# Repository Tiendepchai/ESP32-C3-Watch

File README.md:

# ESP32-C3 ANCS Watch

**ESP32-C3 ANCS Watch** is an ESP-IDF firmware project for a compact BLE watch-style accessory.  
It pairs with an iPhone, subscribes to Apple Notification Center Service (ANCS), fetches notification attributes, synchronizes time, and renders notifications on a 128 × 64 SH1106 OLED display.

> **Project status:** Active firmware prototype. The core BLE/ANCS/display flow is implemented; power monitoring and iOS companion features are optional or under development.

---

## Table of Contents

- [Overview](#overview)
- [Key Features](#key-features)
- [System Architecture](#system-architecture)
- [Hardware](#hardware)
- [Firmware Layout](#firmware-layout)
- [Notification Ordering](#notification-ordering)
- [Getting Started](#getting-started)
- [Build and Flash](#build-and-flash)
- [Usage](#usage)
- [Testing Checklist](#testing-checklist)
- [Troubleshooting](#troubleshooting)
- [Roadmap](#roadmap)
- [License](#license)

---

## Overview

The firmware implements the standard ANCS accessory flow:

1. The ESP32-C3 advertises as a BLE peripheral.
2. The iPhone connects and creates a secure BLE bond.
3. After encryption is enabled, the ESP32-C3 switches role logically to a GATT client and discovers ANCS on the iPhone.
4. The ESP32-C3 subscribes to the ANCS Notification Source and Data Source characteristics.
5. For each notification UID, the firmware requests:
   - `AppIdentifier`
   - `Title`
   - `Message`
   - `Date`
6. Notifications are stored locally and sorted with the newest notification first.
7. The display manager renders connection status, watchface, notification detail, and navigation views.

---

## Key Features

- BLE pairing and bonding powered by NimBLE.
- Bonded reconnect flow using directed advertising first, then general advertising fallback.
- ANCS discovery, CCCD subscription, notification event handling, and attribute parsing.
- Date-based notification ordering using ANCS `Date` when available.
- Temporary local receive timestamp while waiting for notification attributes.
- iOS Current Time Service client for watchface time synchronization.
- SH1106 128 × 64 OLED rendering for:
  - connection status
  - watchface
  - notification list/detail
  - navigation state
- In-memory notification store with configurable filtering.
- NVS-backed settings and bond state persistence.
- Two-button physical control for:
  - notification navigation
  - clearing notifications
  - changing filters
  - resetting bond state
- Optional SwiftUI companion scaffold for future configuration and navigation handoff.

---

## System Architecture

```text
┌────────────────────┐
│      iPhone        │
│  ANCS + CTS Server │
└─────────┬──────────┘
          │ BLE encrypted link
          ▼
┌──────────────────────────────────────┐
│              ESP32-C3                │
│                                      │
│  ┌───────────────┐   ┌────────────┐  │
│  │ BLE Manager   │──▶│ ANCS Client│  │
│  └───────┬───────┘   └─────┬──────┘  │
│          │                 │         │
│          ▼                 ▼         │
│  ┌───────────────┐   ┌─────────────┐ │
│  │ CTS Client    │   │ Notification│ │
│  │ Time Sync     │   │ Store       │ │
│  └───────┬───────┘   └─────┬───────┘ │
│          │                 │         │
│          ▼                 ▼         │
│  ┌────────────────────────────────┐  │
│  │        Display Manager         │  │
│  │      SH1106 OLED Rendering     │  │
│  └────────────────────────────────┘  │
│                                      │
│  ┌────────────────────────────────┐  │
│  │        Storage Manager         │  │
│  │        NVS Settings/Bonds      │  │
│  └────────────────────────────────┘  │
└──────────────────────────────────────┘
```

---

## Hardware

| Component | Specification |
| --- | --- |
| MCU | ESP32-C3 |
| Display | SH1106 128 × 64 OLED |
| Display bus | I2C |
| Button A | GPIO3, active low |
| Button B | GPIO4, active low |

### Default Wiring

| Function | ESP32-C3 Pin |
| --- | --- |
| OLED VCC | 3V3 |
| OLED GND | GND |
| OLED SDA | GPIO6 |
| OLED SCL | GPIO7 |
| Button A | GPIO3 to GND |
| Button B | GPIO4 to GND |

Board-level constants are defined in:

```text
components/board_config/include/board_config.h
```

---

## Firmware Layout

| Path | Purpose |
| --- | --- |
| `main/` | Application state machine, UI flow, and event orchestration |
| `components/ble_manager/` | NimBLE initialization, advertising, bonding, reconnect, and config GATT service |
| `components/ancs_client/` | ANCS discovery, notification subscription, attribute request, and response parser |
| `components/cts_client/` | iOS Current Time Service client |
| `components/display_manager/` | SH1106 driver, framebuffer, watchface rendering, and notification rendering |
| `components/notification_store/` | In-memory notification storage, filtering, and sorting |
| `components/storage_manager/` | NVS-backed settings and persistent state |
| `components/power_manager/` | Optional battery and power monitoring |
| `ios/ANCSWatchConfig/` | Optional SwiftUI companion app scaffold |

---

## Notification Ordering

The notification ordering pipeline is designed to avoid relying only on local receive time.

```text
ANCS Notification Source event
        │
        ▼
Extract NotificationUID
        │
        ▼
Request attributes:
AppIdentifier, Title, Message, Date
        │
        ▼
Parse ANCS Data Source response
        │
        ▼
Use ANCS Date if available
        │
        ▼
Update notification record
        │
        ▼
Sort newest first
```

When a notification event first arrives, the firmware stores it with the local receive timestamp as a temporary value.  
After the ANCS `Date` attribute is fetched, the stored record is updated and the notification list is re-sorted by timestamp in descending order.

This allows notifications such as:

```text
Messenger  - 1 second ago
MoMo       - 2 minutes ago
```

to appear in the expected order, with the newest notification at the top.

---

## Getting Started

### Prerequisites

Install and configure:

- ESP-IDF v6.0 or newer
- Python environment required by ESP-IDF
- USB serial driver for your ESP32-C3 board
- An iPhone with Bluetooth enabled
- Optional: nRF Connect for BLE debugging

### Clone the Repository

```bash
git clone <your-repository-url>
cd esp32-c3-ancs-watch
```

### Set the ESP-IDF Target

```bash
idf.py set-target esp32c3
```

---

## Build and Flash

### Activate ESP-IDF

Use the activation script generated by your ESP-IDF installation.

Example:

```bash
source "$HOME/.espressif/tools/activate_idf_v6.0.sh"
```

Alternatively, if ESP-IDF is installed globally:

```bash
. "$IDF_PATH/export.sh"
```

### Build

```bash
idf.py build
```

### Flash

Replace the port with the serial device used by your board.

```bash
idf.py -p /dev/cu.usbmodemXXXX flash
```

### Monitor Logs

```bash
idf.py -p /dev/cu.usbmodemXXXX monitor
```

### Flash and Monitor in One Command

```bash
idf.py -p /dev/cu.usbmodemXXXX flash monitor
```

---

## Usage

### First Pairing

1. Flash the firmware to the ESP32-C3.
2. Open the Bluetooth settings on iOS.
3. Select the ESP32-C3 accessory.
4. Accept the pairing request.
5. Wait until the BLE link is encrypted and ANCS discovery completes.
6. Send a test notification to the iPhone.
7. Verify that the OLED displays the notification.

### Reconnect Flow

After a successful bond, the firmware tries:

1. Directed advertising to the bonded iPhone.
2. General advertising fallback if directed reconnect fails.
3. ANCS rediscovery after the encrypted link is restored.

### Button Controls

| Action | Expected Behavior |
| --- | --- |
| Button A | Navigate through notifications or UI views |
| Button B | Change filter, clear notification, or trigger secondary action |
| Long press / configured combo | Reset bond state or enter maintenance flow |

> Exact button behavior depends on the current firmware state machine and board configuration.

---

## Testing Checklist

Before testing a first-pair flow:

- Clear the iOS Bluetooth bond for the ESP32-C3.
- Clear stored bonds on the ESP32-C3.
- Reboot both devices if bonding behavior is inconsistent.

Recommended validation sequence:

- Pair from iOS or nRF Connect.
- Confirm the first bond is retained locally.
- Check logs for:

```text
bond store peers after secure=1
```

- Wait for:

```text
ANCS ready, attrs=enabled
```

- Send several notifications from different apps.
- Verify that notification details are fetched correctly.
- Verify that notifications are sorted by ANCS `Date`.
- Walk out of range to force a disconnect.
- Return to range and confirm bonded reconnect works.
- Confirm pre-existing or pending notifications can wake the display and render correctly.
- Test button navigation, filter changes, clear action, and bond reset.

---

## Troubleshooting

### ANCS does not become ready

Check that:

- The iPhone accepted the BLE pairing request.
- The connection is encrypted.
- The ESP32-C3 bond was not erased after pairing.
- ANCS discovery runs only after encryption.
- Notification permissions are enabled on iOS.

Useful log marker:

```text
ANCS ready, attrs=enabled
```

### Notifications appear but details are missing

Check that:

- Data Source subscription succeeded.
- Control Point writes are accepted.
- `GetNotificationAttributes` is sent with the correct `NotificationUID`.
- The parser handles fragmented Data Source responses.

### Notification order is incorrect

Check that:

- `Date` is included in the requested ANCS attributes.
- The firmware updates the temporary receive timestamp after `Date` arrives.
- The notification store re-sorts the list after attribute parsing.

### Reconnect does not work

Check that:

- Bond data is stored in NVS.
- Directed advertising uses the bonded peer address.
- General advertising fallback starts after directed advertising fails.
- iOS still has the accessory saved in Bluetooth settings.

### macOS ESP-IDF `platform.mac_ver()` issue

If the local Python environment fails because of a macOS version parsing issue, use a clean ESP-IDF Python environment first.  
If the issue persists, the following development workaround can be used:

```bash
IDF_COMPONENT_MANAGER=0 python -c 'import os, platform, runpy, sys; tools=os.path.join(os.environ["IDF_PATH"],"tools"); sys.path.insert(0,tools); platform.mac_ver=lambda release="", versioninfo=("", "", ""), machine="": ("26.1", ("", "", ""), os.uname().machine); sys.argv=[os.path.join(tools,"idf.py")]+sys.argv[1:]; runpy.run_path(sys.argv[0], run_name="__main__")' build
```

---

## Roadmap

- [ ] Add battery percentage monitoring.
- [ ] Add charging status display.
- [ ] Improve notification grouping by app.
- [ ] Add persistent notification history if required.
- [ ] Finalize iOS SwiftUI companion app.
- [ ] Add configurable button actions.
- [ ] Add screenshots or hardware photos.
- [ ] Add CI build workflow for ESP-IDF.
- [ ] Add release binaries and flashing instructions.

---

## License

This project is licensed under the MIT License. See [LICENSE](LICENSE) for details.

---

## Vietnamese Summary

**ESP32-C3 ANCS Watch** là firmware ESP-IDF cho thiết bị đeo nhỏ dùng BLE. Thiết bị ghép đôi với iPhone, subscribe Apple Notification Center Service, lấy thông tin `AppIdentifier`, `Title`, `Message`, `Date`, sau đó hiển thị thông báo lên OLED SH1106 128 × 64.

Điểm chính:

- Pairing/bonding BLE bằng NimBLE.
- Tự reconnect với iPhone đã bond.
- Fetch chi tiết thông báo qua ANCS.
- Sort thông báo theo `Date` để thông báo mới nhất hiện trên đầu.
- Đồng bộ giờ qua iOS Current Time Service.
- Hiển thị watchface và notification bằng SH1106 OLED.
- Lưu cấu hình bằng NVS.
- Điều khiển bằng hai nút vật lý.

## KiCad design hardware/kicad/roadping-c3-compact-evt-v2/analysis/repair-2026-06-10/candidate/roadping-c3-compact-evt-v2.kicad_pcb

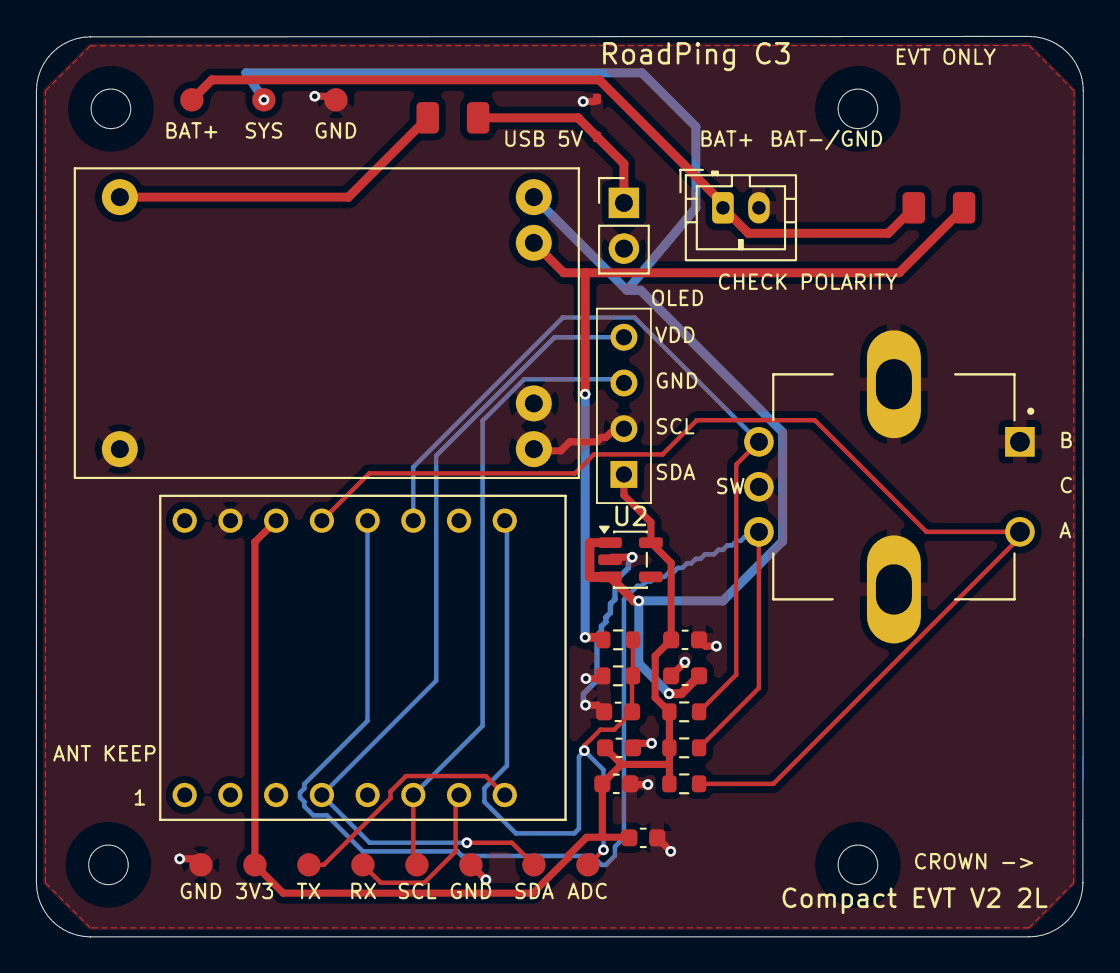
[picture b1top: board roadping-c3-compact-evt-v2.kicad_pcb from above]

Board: 2 copper layers, 58.2 x 50.0 mm, 31 parts (0 on the bottom side), 15 nets.

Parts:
C1, C2: 1uF; C_0603_1608Metric
C3: 10uF; C_0603_1608Metric
C4, C5, C9: 100nF; C_0603_1608Metric
D1: USB_5V_TVS; D_SOD-323
DS1: SH1106_I2C_OLED; OLED_4PIN_VDD_GND_SCK_SDA_2.54MM
F1: PTC_USB_5V_1A; Fuse_1206_3216Metric
F2: PTC_BAT_1A; Fuse_1206_3216Metric
J1: USB_5V_INPUT; PinHeader_1x02_P2.54mm_Vertical
J2: JST_PH_2PIN_LIPO; JST_PH_B2B-PH-K_1x02_P2.00mm_Vertical
J3: UART_DEBUG_PROGRAM; TESTPADS_1X06_2.54MM_EVT
MH1, MH2, MH3, MH4: M2_NPTH; MountingHole_M2_NPTH_5mmKeepout
R3, R4, R5: 10k; R_0603_1608Metric
R6: 220k; R_0603_1608Metric
R7: 100k; R_0603_1608Metric
SW1: PEC11R-4215F-S0024; XDCR_PEC11R-4215F-S0024
TP2: BAT_CONN+; TP_Round_1.0mm
TP3: SYS_RAW; TP_Round_1.0mm
TP5: GND; TP_Round_1.0mm
TP8: I2C_SDA; TP_Round_1.0mm
TP13: BAT_ADC; TP_Round_1.0mm
U1: TP4056-Module
U2: AP2112K-3.3; SOT-23-5
U3: ESP32-C3_SUPERMINI_TH; MODULE_ESP32-C3_SUPERMINI_TH

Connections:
/3V3: C2.1, C3.1, C4.1, C5.1, DS1.1 (VDD), J3.2, R3.1, R4.1, R5.1, U2.5 (VOUT), U3.3.3 (3V3)
/BAT_ADC: C9.1, R6.2, R7.1, TP13.1 (1_1), U3.0 (GPIO0)
/BAT_CONN+: F2.1, J2.1 (BAT+), TP2.1 (1_1)
/ENC_A: R3.2, SW1.A, U3.2 (GPIO2)
/ENC_B: R4.2, SW1.B, U3.3 (GPIO3)
/ENC_SW: R5.2, SW1.2 (SW2), U3.4 (GPIO4)
/GND: C1.2, C2.2, C3.2, C4.2, C5.2, C9.2, D1.1, DS1.2 (GND), J1.2, J2.2 (BAT-), J3.1, J3.6, R7.2, SW1.1 (SW1), SW1.C, SW1.S1 (SHIELD1), SW1.S2 (SHIELD2), TP5.1 (1_1), U1.2 (IN-), U1.4 (OUT-), U1.6 (B-), U2.2 (GND), U3.G (GND)
/I2C_SCL: DS1.3 (SCK), J3.5, U3.10 (GPIO10)
/I2C_SDA: DS1.4 (SDA), TP8.1 (1_1), U3.8 (GPIO8)
/SYS_RAW: C1.1, TP3.1 (1_1), U1.3 (OUT+), U2.1 (VIN), U2.3 (EN)
/UART_RX: J3.4, U3.20 (GPIO20)
/UART_TX: J3.3, U3.21 (GPIO21)
/USB_5V: F1.2, U1.1 (IN+)
/USB_5V_IN: D1.2, F1.1, J1.1
/VBAT: F2.2, R6.1, U1.5 (B+)

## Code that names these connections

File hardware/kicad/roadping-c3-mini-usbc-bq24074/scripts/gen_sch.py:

#!/usr/bin/env python3
"""RoadPing C3 Mini KiCad 10 schematic generator — CLEAN"""
import os, uuid as _u, subprocess, json
from datetime import date

PROJ = os.path.dirname(os.path.dirname(os.path.abspath(__file__)))
SCH = os.path.join(PROJ, "roadping-c3-mini-usbc-bq24074.kicad_sch")
U = lambda: str(_u.uuid4())
G = 2.54; grd = lambda v: round(v/G)*G
_ = lambda x: f'\t\t{x}'  # indent level

def gl(name,x,y,o=0): return f'\t(global_label "{name}" (shape input) (at {grd(x)} {grd(y)} {o}) (effects (font (size 1.27 1.27))) (uuid "{U()}"))'
def w(x1,y1,x2,y2): return f'\t(wire (pts (xy {grd(x1)} {grd(y1)}) (xy {grd(x2)} {grd(y2)})) (stroke (width 0) (type default)) (uuid "{U()}"))'
def ll(name,x,y): return f'\t(label "{name}" (at {grd(x)} {grd(y)} 0) (effects (font (size 1.27 1.27))) (uuid "{U()}"))'

def SYM(lib_id, ref, val, x, y, fp="", ds=""):
    x,y = grd(x), grd(y); u = U()
    p = [f'(property "Reference" "{ref}" (at {x} {y-3.81} 0) (show_name no) (do_not_autoplace no) (effects (font (size 1.27 1.27))))',
         f'(property "Value" "{val}" (at {x} {y+3.81} 0) (show_name no) (do_not_autoplace no) (effects (font (size 1.27 1.27))))']
    if fp: p.append(f'(property "Footprint" "{fp}" (at {x} {y} 0) (hide yes) (show_name no) (do_not_autoplace no) (effects (font (size 1.27 1.27))))')
    if ds: p.append(f'(property "Datasheet" "{ds}" (at {x} {y} 0) (hide yes) (show_name no) (do_not_autoplace no) (effects (font (size 1.27 1.27))))')
    return f'\n\t(symbol (lib_id "{lib_id}") (at {x} {y} 0) (unit 1) (exclude_from_sim no) (in_bom yes) (on_board yes) (uuid "{u}")\n\t\t{chr(10).join(p)}\n\t)'

def GND(x,y):
    x,y = grd(x), grd(y); u = U()
    return f'\n\t(symbol (lib_id "roadping-c3:GND") (at {x} {y} 0) (unit 1) (in_bom no) (on_board no) (uuid "{u}") (property "Value" "GND" (at {x} {y+2.54} 0) (show_name no) (do_not_autoplace no) (effects (font (size 1.27 1.27)))))'

def PWR(x,y):
    x,y = grd(x), grd(y); u = U()
    return f'\n\t(symbol (lib_id "roadping-c3:PWR_FLAG") (at {x} {y} 0) (unit 1) (in_bom no) (on_board no) (uuid "{u}") (property "Value" "PWR_FLAG" (at {x} {y+2.54} 0) (show_name no) (do_not_autoplace no) (effects (font (size 1.27 1.27)))))'

# ── Build ─────────────────────────────────────────────────────
L = []
L.append(f'(kicad_sch\n\t(version 20260306)\n\t(generator "eeschema")\n\t(generator_version "10.0")\n\t(uuid "{U()}")\n\t(paper "A4")\n\t(title_block\n\t\t(title "RoadPing C3 Mini - USB-C + BQ24074")\n\t\t(date "{date.today().isoformat()}")\n\t\t(rev "schematic-draft")\n\t\t(company "RoadPing")\n\t)')

# Embed symbols from a file read
embed_file = os.path.join(PROJ, 'scripts', 'EMBED.txt')
if os.path.exists(embed_file):
    with open(embed_file) as f:
        embed = f.read()
else:
    embed = ''
    sys.stderr.write("WARNING: EMBED.txt not found, creating minimal schematic\n")

L.append(f'\t(lib_symbols\n{embed}\t)')

# 1. USB-C
L.append(SYM("Connector_USB:USB_C_Receptacle_USBIF","J1","TYPE-C-31-M-12",50.8,50.8,fp="Connector_USB:USB_C_Receptacle_HRO_TYPE-C-31-M-12"))
L.append(SYM("roadping-c3:Fuse","F1","PTC 1.1A",76.2,50.8))
L.append(SYM("roadping-c3:D_TVS","D1","PESD5V0S1BA",76.2,68.58))
L.append(SYM("roadping-c3:R","R1","5.1k",76.2,78.74))
L.append(SYM("roadping-c3:R","R2","5.1k",76.2,86.36))
L.append(SYM("Interface_Protection:USBLC6-2SC6","D2","USBLC6-2SC6",106.68,53.34))
L.append(w(60.96,50.8,76.2,50.8))
L.append(gl("VBUS",76.2,63.5)); L.append(w(76.2,58.42,76.2,68.58)); L.append(GND(76.2,71.12))
L.append(ll("CC1",66.04,78.74)); L.append(w(66.04,78.74,76.2,78.74)); L.append(GND(76.2,81.28))
L.append(ll("CC2",66.04,86.36)); L.append(w(66.04,86.36,76.2,86.36)); L.append(GND(76.2,88.9))
L.append(ll("USB_DP",66.04,43.18)); L.append(ll("USB_DN",66.04,38.1))
L.append(w(66.04,43.18,96.52,43.18)); L.append(w(66.04,38.1,96.52,38.1))
L.append(gl("USB_DP",115.06,43.18)); L.append(gl("USB_DN",115.06,38.1))

# 2. BQ24074
L.append(SYM("Battery_Management:BQ24074_RGT","U1","BQ24074RGTR",50.8,119.38,fp="Package_DFN_QFN:WQFN-20-1EP_3.5x3.5mm_P0.5mm_EP2.7x2.7mm",ds="https://www.ti.com/lit/ds/symlink/bq24074.pdf"))
L.append(gl("VBUS",40.64,119.38)); L.append(w(40.64,119.38,50.8,119.38))
L.append(SYM("roadping-c3:R","R3","1.1k",33.02,137.16))
L.append(SYM("roadping-c3:R","R4","2.0k",33.02,142.24))
L.append(GND(33.02,133.35)); L.append(GND(33.02,138.43))
L.append(SYM("roadping-c3:R","R5","10k",73.66,129.54))
L.append(SYM("roadping-c3:R","R6","10k",73.66,134.62))
L.append(GND(73.66,137.16))
L.append(SYM("roadping-c3:R","R_CE","10k",76.2,109.22))
L.append(SYM("roadping-c3:R","R_CHG","10k",76.2,104.14))
L.append(SYM("roadping-c3:R","R_FLT","10k",76.2,99.06))
L.append(gl("3V3",83.82,114.3)); L.append(gl("CE_CHG",83.82,109.22))
L.append(gl("CHG_STAT",83.82,104.14)); L.append(gl("FLT_STAT",83.82,99.06))
L.append(gl("SYS_RAW",76.2,119.38)); L.append(gl("VBAT",76.2,127.0))

# 3. AP2112K + LiPo
L.append(SYM("roadping-c3:AP2112K-3.3","U2","AP2112K-3.3",139.7,119.38))
L.append(SYM("roadping-c3:C","C1","1uF",129.54,129.54))
L.append(SYM("roadping-c3:C","C2","1uF",129.54,134.62))
L.append(SYM("roadping-c3:C","C3","10uF",154.94,129.54))
L.append(SYM("roadping-c3:Fuse","F2","PTC 1.1A",157.48,119.38))
L.append(SYM("roadping-c3:Conn_01x02","J2","JST-PH LiPo",170.18,124.46,fp="Connector_JST:JST_PH_B2B-PH-K_1x02_P2.00mm_Vertical"))
L.append(gl("SYS_RAW",129.54,119.38)); L.append(gl("3V3",154.94,116.84))
L.append(gl("VBAT",154.94,124.46))
L.append(GND(129.54,127.0)); L.append(GND(129.54,132.08)); L.append(GND(154.94,127.0))
L.append(GND(170.18,121.92))

# 4. ESP32-C3-MINI-1
MX, MY = 248.92, 50.8
L.append(SYM("roadping-c3:ESP32-C3-MINI-1-N4","U3","ESP32-C3-MINI-1-N4",MX,MY))

left_pins = [(0,25.4,"GPIO0"),(1,22.86,"GPIO1"),(2,20.32,"GPIO2"),(3,17.78,"GPIO3"),(4,15.24,"GPIO4"),
    (5,12.7,"GPIO5"),(6,10.16,"GPIO6"),(7,7.62,"GPIO7"),(8,5.08,"I2C_SDA"),(9,2.54,"GPIO9"),(10,0,"I2C_SCL"),
    (18,-15.24,"GPIO18"),(19,-17.78,"GPIO19"),(20,-20.32,"GPIO20"),(21,-22.86,"GPIO21")]
for pn,py,ln in left_pins:
    L.append(w(MX-22.86, MY+py, MX-20.32, MY+py))
    L.append(gl(ln, MX-22.86, MY+py))
for py in [25.4,22.86,20.32,17.78,15.24,12.7]:
    L.append(w(MX+20.32, MY+py, MX+22.86, MY+py))
    L.append(gl("3V3", MX+22.86, MY+py))
for py in [-5.08,-7.62,-10.16]:
    L.append(w(MX+20.32, MY+py, MX+22.86, MY+py))
    L.append(GND(MX+25.4, MY+py))
L.append(gl("CE_CHG",MX-30.48,MY+15.24))
L.append(gl("CHG_STAT",MX-30.48,MY+12.7))
L.append(gl("FLT_STAT",MX-30.48,MY+10.16))
L.append(gl("I2C_SDA",MX-30.48,MY+7.62))
L.append(gl("I2C_SCL",MX-30.48,MY+5.08))
L.append(gl("GPIO2",MX-22.86,MY+22.86))
L.append(gl("GPIO3",MX-22.86,MY+20.32))
L.append(gl("GPIO4",MX-22.86,MY+17.78))

# 5. Peripherals
L.append(SYM("roadping-c3:OLED_128X64_1.3_I2C","DS1","SH1106 OLED",88.9,243.84))
L.append(gl("3V3",104.14,243.84)); L.append(GND(104.14,238.76))
L.append(gl("I2C_SCL",78.74,243.84)); L.append(gl("I2C_SDA",78.74,238.76))
L.append(SYM("roadping-c3:PEC11R-4215F-S0024","SW1","PEC11R",154.94,243.84))
L.append(SYM("roadping-c3:R","R7","10k",144.78,241.3))
L.append(SYM("roadping-c3:R","R8","10k",144.78,236.22))
L.append(SYM("roadping-c3:R","R9","10k",144.78,231.14))
L.append(gl("3V3",137.16,243.84))
L.append(gl("GPIO2",170.18,243.84)); L.append(gl("GPIO3",170.18,238.76)); L.append(gl("GPIO4",170.18,233.68))
L.append(SYM("Transistor_FET:BSS138","Q1","BSS138",88.9,269.24,fp="Package_TO_SOT_SMD:SOT-23"))
L.append(SYM("roadping-c3:R","R10","470k",78.74,266.7))
L.append(SYM("roadping-c3:R","R11","470k",78.74,271.78))
L.append(SYM("roadping-c3:R","R12","100k",78.74,276.86))
L.append(SYM("roadping-c3:C","C9","100nF",104.14,269.24))
L.append(gl("VBAT",73.66,266.7)); L.append(gl("GPIO0",109.22,266.7)); L.append(gl("GPIO1",109.22,271.78))
L.append(GND(104.14,264.18)); L.append(GND(78.74,274.32)); L.append(GND(78.74,279.4))

L.append(SYM("roadping-c3:Conn_01x02","SW2","BOOT",210.82,269.24))
L.append(gl("GPIO9",205.74,269.24)); L.append(GND(210.82,264.18))

L.append(SYM("roadping-c3:TestPoint","TP_TX","UART_TX",279.4,248.92))
L.append(SYM("roadping-c3:TestPoint","TP_RX","UART_RX",279.4,241.3))
L.append(gl("GPIO20",274.32,248.92)); L.append(gl("GPIO21",274.32,241.3))

L.append('\n\t(sheet_instances\n\t\t(path "/" (page "1"))\n\t)\n\t(symbol_instances)\n)')

with open(SCH,"w") as f: f.write('\n'.join(L))
print(f"✅ Written {SCH} — {len(L)} lines")

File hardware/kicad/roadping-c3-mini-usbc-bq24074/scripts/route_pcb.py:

#!/usr/bin/env python3
"""RoadPing C3 Mini — PCB routing generator.
   Applies traces + vias + zones to the placed PCB."""
import os, sys, re, uuid as _u

PROJ = os.path.dirname(os.path.dirname(os.path.abspath(__file__)))
PCB = os.path.join(PROJ, "roadping-c3-mini-usbc-bq24074.kicad_pcb")
U = lambda: str(_u.uuid4())

# ── Read existing PCB ────────────────────────────────────────────
with open(PCB) as f:
    pcb_text = f.read()

# Find net IDs and footprint positions
# KiCad auto-assigns net numbers. We'll use net 0 as common GND placeholder.
# In practice, nets are assigned by netlist import from schematic.

# ── Routing data ─────────────────────────────────────────────────
# segment: (x1,y1, x2,y2, width, layer)
SEGMENTS = []
# via: (x, y, diameter, drill, layers)
VIAS = []
# zone: (layer, net, polygon_points, priority)
ZONES = []

def seg(x1, y1, x2, y2, w, layer="F.Cu"):
    SEGMENTS.append((x1, y1, x2, y2, w, layer))

def via(x, y, dia=0.6, drill=0.3, layers=("F.Cu","B.Cu")):
    VIAS.append((x, y, dia, drill, layers))

def zone(layer, net, pts, priority=0):
    ZONES.append((layer, net, pts, priority))

# ── Power traces (0.5mm, F.Cu) ───────────────────────────────────
# VBUS: J1(12,25) → F1(22,15) → F1→D1(22,20) → VBUS_FILT to BQ24074
# J1 connector at (12,25) — VBUS pins at right side
# F1 at (22,15) — pin1 at left, pin2 at right
seg(14.0, 25.0, 20.0, 15.0, 0.5)  # J1 VBUS → F1-1
seg(24.0, 15.0, 22.0, 20.0, 0.5)  # F1-2 → D1 K (shared VBUS_FILT)
seg(24.0, 20.0, 32.0, 32.0, 0.5)  # D1 → BQ24074 IN (U1 at 32,32)

# SYS_RAW: BQ24074 OUT → F2 → J2 → AP2112K VIN
seg(32.0, 34.0, 48.0, 26.0, 0.5)  # BQ24074 OUT → U2 VIN
seg(44.0, 26.0, 44.0, 25.0, 0.5)  # branch to C1-1
seg(48.0, 26.0, 52.0, 35.0, 0.5)  # U2 → F2
seg(54.0, 35.0, 58.0, 35.0, 0.5)  # F2 → J2

# 3V3: AP2112K VOUT → ESP32-C3 + peripherals
seg(48.0, 30.0, 48.0, 32.0, 0.4)  # U2 VOUT towards C2
seg(48.0, 30.0, 52.0, 25.0, 0.4)  # U2 VOUT → C3
# ESP32-C3 VDD right-side pins at (55,30) + (20.32, varied y)
# Module center (55,30), right row at x=55+20.32=75.32, y=30+25.4=55.4 etc.
# 3V3 trace along right side of module
seg(61.0, 28.0, 61.0, 15.5, 0.4)  # decap chain (C4-C9)

# ── USB differential pair (90Ω, 0.3mm, 0.15mm gap) ──────────────
# J1 D+/D- → USBLC6 → 27R → ESP32-C3
# J1 at (12,25) — D+ pin, D- pin
# USBLC6 (D2) at (32,20)
# 27R R13 at (36,18), R14 at (36,22)
# ESP32-C3 at (55,30) — USB_DP at (75.32, 7.14), USB_DN at (75.32, 4.6)

# USB_DP: J1 → D2-1 → D2-6 → R13 → U3
seg(16.0, 26.5, 30.0, 20.0, 0.3)   # J1 D+ → D2 (shared)
seg(34.0, 20.0, 36.0, 18.0, 0.3)   # D2-6 → R13-1
seg(36.0, 18.0, 72.0, 18.0, 0.3)   # R13-2 → right side of board
seg(72.0, 18.0, 72.0, 7.14, 0.3)   # down to U3 USB_DP pin (y=30+(-22.86)=7.14)

# USB_DN: J1 → D2-3 → D2-4 → R14 → U3
seg(16.0, 23.5, 30.0, 18.0, 0.3)   # J1 D- → D2
seg(34.0, 18.0, 36.0, 22.0, 0.3)   # D2-4 → R14-1
seg(36.0, 22.0, 72.0, 22.0, 0.3)   # R14-2 → right side of board
seg(72.0, 22.0, 72.0, 4.6, 0.3)    # down to U3 USB_DN pin (y=30+(-25.4)=4.6)

# ── I2C traces (0.25mm, orthogonal, ≥0.2mm clearance) ──────────
# ESP32-C3 GPIO8(SDA) at (55-20.32, 30+5.08) = (34.68, 35.08)
# GPIO10(SCL) at (34.68, 30.0)
# OLED DS1 at (20,45): pin3(SCK) at (-15.24,2.54), pin4(SDA) at (-15.24,0)
# Route SDA: GPIO8 → right to 36, down to 36, left to OLED
seg(34.68, 35.08, 36.0, 35.08, 0.25)  # SDA right
seg(36.0, 35.08, 36.0, 44.0, 0.25)    # SDA down
seg(36.0, 44.0, 20.0, 44.0, 0.25)     # SDA left to OLED area
# Route SCL: GPIO10 → right to 38, down to 46, left to OLED
seg(34.68, 30.0, 38.0, 30.0, 0.25)    # SCL right
seg(38.0, 30.0, 38.0, 46.0, 0.25)     # SCL down
seg(38.0, 46.0, 20.0, 46.0, 0.25)     # SCL left to OLED area
# Final approaches to OLED pins
seg(20.0, 44.0, 20.0, 42.0, 0.25)     # SDA up to OLED SDA pin
seg(20.0, 46.0, 20.0, 44.5, 0.25)     # SCL up to OLED SCK pin

# ── Encoder traces (0.25mm) ──────────────────────────────────────
# GPIO2 at (34.68, 50.32), GPIO3 at (34.68, 47.78), GPIO4 at (34.68, 45.24)
# SW1 at (50,44): A=GPIO2, B=GPIO3, SW=GPIO4
seg(34.68, 50.32, 42.0, 43.0, 0.25)  # GPIO2 → R7/encoder A
seg(34.68, 47.78, 42.0, 45.5, 0.25)  # GPIO3 → R8/encoder B
seg(34.68, 45.24, 45.0, 48.0, 0.25)  # GPIO4 → R9/encoder SW

# ── Charger status (0.25mm) ──────────────────────────────────────
# GPIO5-7 from ESP32 left side → pull-ups → BQ24074
# GPIO5 at (34.68, 42.7), GPIO6 at (34.68, 40.16), GPIO7 at (34.68, 37.62)
# R_CE (38,25), R_CHG (38,22), R_FLT (38,19)
seg(34.68, 42.7, 38.0, 25.0, 0.25)   # CE
seg(34.68, 40.16, 38.0, 22.0, 0.25)  # CHG
seg(34.68, 37.62, 38.0, 19.0, 0.25)  # FLT/FAULT

# ── Battery ADC (0.25mm) ─────────────────────────────────────────
# R10(15,39): VBAT → 470k
# R11(15,42): 470k → BSS138 drain
# R12(15,45): GPIO1 → 100k → GND
# Q1(20,41): gate=GPIO1
# GPIO1 at (34.68, 52.86), GPIO0/BAT_SENSE at (34.68, 55.4)
seg(34.68, 52.86, 15.0, 45.0, 0.25)  # GPIO1 → R12/1, Q1 gate
seg(34.68, 55.4, 15.0, 42.0, 0.25)   # BAT_SENSE → divider jct
seg(15.0, 39.0, 15.0, 42.0, 0.25)     # divider series R10→R11
seg(15.0, 42.0, 20.0, 41.0, 0.25)     # divider jct → Q1 drain

# ── BOOT button ──────────────────────────────────────────────────
# GPIO9 at (34.68, 33.62) → SW2(65,44) → GND
seg(34.68, 33.62, 65.0, 44.0, 0.25)

# ── UART test points ─────────────────────────────────────────────
# GPIO20 at (34.68, 9.68), GPIO21 at (34.68, 7.14)
# TP_RX(72,46), TP_TX(72,42)
seg(34.68, 9.68, 72.0, 42.0, 0.25)   # GPIO20 → TP_RX
seg(34.68, 7.14, 72.0, 46.0, 0.25)   # GPIO21 → TP_TX

# ── GND vias (stitching around ESP32-C3 module) ──────────────────
# Place GND vias around module to connect F.Cu GND to In1.Cu GND plane
for gx in [45, 50, 55, 60, 65]:
    for gy in [20, 25, 35, 40]:
        via(gx, gy)

# Thermal vias under BQ24074 (center at 32,32)
for tx in [31, 32, 33]:
    for ty in [31, 32, 33]:
        via(tx, ty, 0.5, 0.3)

# ── Zone pours ──────────────────────────────────────────────────
# Full GND plane on In1.Cu
zone("In1.Cu", 0, [(0,0),(80,0),(80,50),(0,50)])
# Split power plane on In2.Cu — VBUS area, SYS_RAW area, 3V3 area
zone("In2.Cu", 0, [(0,0),(30,0),(30,30),(0,30)], 99)  # GND portion
# Top-layer GND pour after routing
zone("F.Cu", 0, [(0,0),(80,0),(80,50),(0,50)], 10)

# ── Write routing to PCB file ────────────────────────────────────
def gen():
    global pcb_text

    # Remove the trailing paren of kicad_pcb
    pcb_text = pcb_text.strip()
    assert pcb_text.endswith(')')
    base = pcb_text[:-1].rstrip()

    lines = [base]

    # Add segments
    for x1, y1, x2, y2, w, layer in SEGMENTS:
        lines.append(f'\t(segment (start {x1:.2f} {y1:.2f}) (end {x2:.2f} {y2:.2f}) (width {w}) (layer "{layer}") (net 0) (uuid "{U()}"))')

    # Add vias
    for x, y, dia, drill, layers in VIAS:
        layer_str = ' '.join(f'"{l}"' for l in layers)
        lines.append(f'\t(via (at {x:.2f} {y:.2f}) (size {dia}) (drill {drill}) (layers {layer_str}) (net 0) (uuid "{U()}"))')

    # ZONES COMMENTED OUT: KiCad 10.0.1 CLI rejects zone syntax
    # Zones will be added via KiCad GUI.
    # For reference:
    # zone("In1.Cu", 0, GND plane polygon)
    # zone("F.Cu", 0, GND pour after routing)

    lines.append(')')

    with open(PCB, 'w') as f:
        f.write('\n'.join(lines))
    print(f"✅ Routed PCB: {len(SEGMENTS)} segments, {len(VIAS)} vias, {len(ZONES)} zones")

if __name__ == "__main__":
    gen()

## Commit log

2026-04-11 Initialize repository
2026-04-11 Add root build configuration
2026-04-11 Add app skeleton and core board components
2026-04-11 Add display manager and SH1106 renderer
2026-04-11 Add ANCS client and parser
2026-04-11 Add BLE manager and config GATT service
2026-04-11 Add NVS-backed storage manager
2026-04-11 Add main app orchestration
2026-04-11 Add iOS config companion scaffold
2026-04-11 Fix iOS BLE config UUIDs
2026-05-19 Fix ANCS reconnect notification handling
2026-05-19 Revise README for clarity and structure improvements
    Updated README.md to enhance clarity and structure, including improved descriptions of features, hardware specifications, and firmware layout.
2026-05-19 Fix formatting in System Architecture diagram
2026-06-18 Add BQ24074 hardware plan
2026-06-18 Add compact EVT analysis artifacts

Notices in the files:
README.md:
License: MIT
